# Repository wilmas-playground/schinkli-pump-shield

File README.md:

# Bewässerungssystem für Pflanzen auf ESP8266

This repository contains the source and manufacturing files for the controller board of 
a plant watering system named _schinkli_. The main concept of the system is to have a controller 
board and shields for it.

## schinkli pump shield

The daughter board for running pumps is named _schinkli pump shield_ and contains two footprints for n-channel FETs and jumpers to assign them to the _brain_'s output.
The main idea is to use both channels for pumps, but they can be used for whatever the FETs can handle (i.e. light bulbs, motors, etc.).

## Project URLs

Software: [schinkli-code](https://github.com/wilmas-playground/schinkli-code)

Controller: [schinkli-brain](https://github.com/wilmas-playground/schinkli-brain)

Pump Drivers: [schinkli-pump-shield](https://github.com/wilmas-playground/schinkli-pump-shield)

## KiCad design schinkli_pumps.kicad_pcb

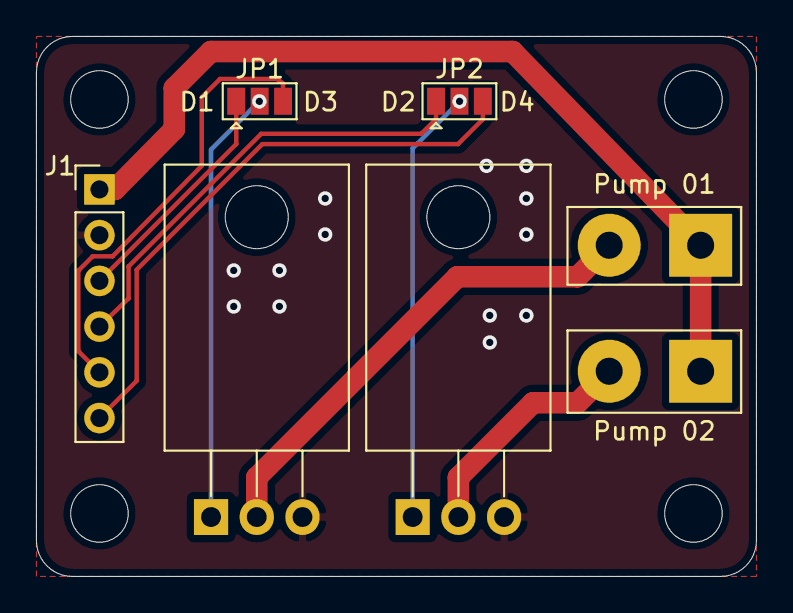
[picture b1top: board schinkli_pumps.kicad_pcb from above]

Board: 2 copper layers, 40.0 x 30.0 mm, 11 parts (0 on the bottom side), 10 nets.

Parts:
J1: BridgeHeader; PinHeader_1x06_P2.54mm_Vertical
J2: Pump 01; SolderWirePad_1x02_P5.08mm_Drill1.5mm
J3: Pump 02; SolderWirePad_1x02_P5.08mm_Drill1.5mm
JP1, JP2: SolderJumper_3_Open; SolderJumper-3_P1.3mm_Open_Pad1.0x1.5mm
Q1, Q2: IRLZ44N; TO-220-3_Horizontal_TabDown
hole1, hole2, hole3, hole4: MountingHole_3.2mm_M3

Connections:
D1: J1.3, JP1.1
D2: J1.4, JP2.1
D3: J1.5, JP1.3
D4: J1.6, JP2.3
GND: J1.2, Q1.3, Q2.3
unnamed: J2.2, Q1.2
unnamed: J3.2, Q2.2
P1: JP1.2, Q1.1
P2: JP2.2, Q2.1
VCC: J1.1, J2.1, J3.1

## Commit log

2020-04-14 add project and production files v1
2020-05-16 add image and update readme
